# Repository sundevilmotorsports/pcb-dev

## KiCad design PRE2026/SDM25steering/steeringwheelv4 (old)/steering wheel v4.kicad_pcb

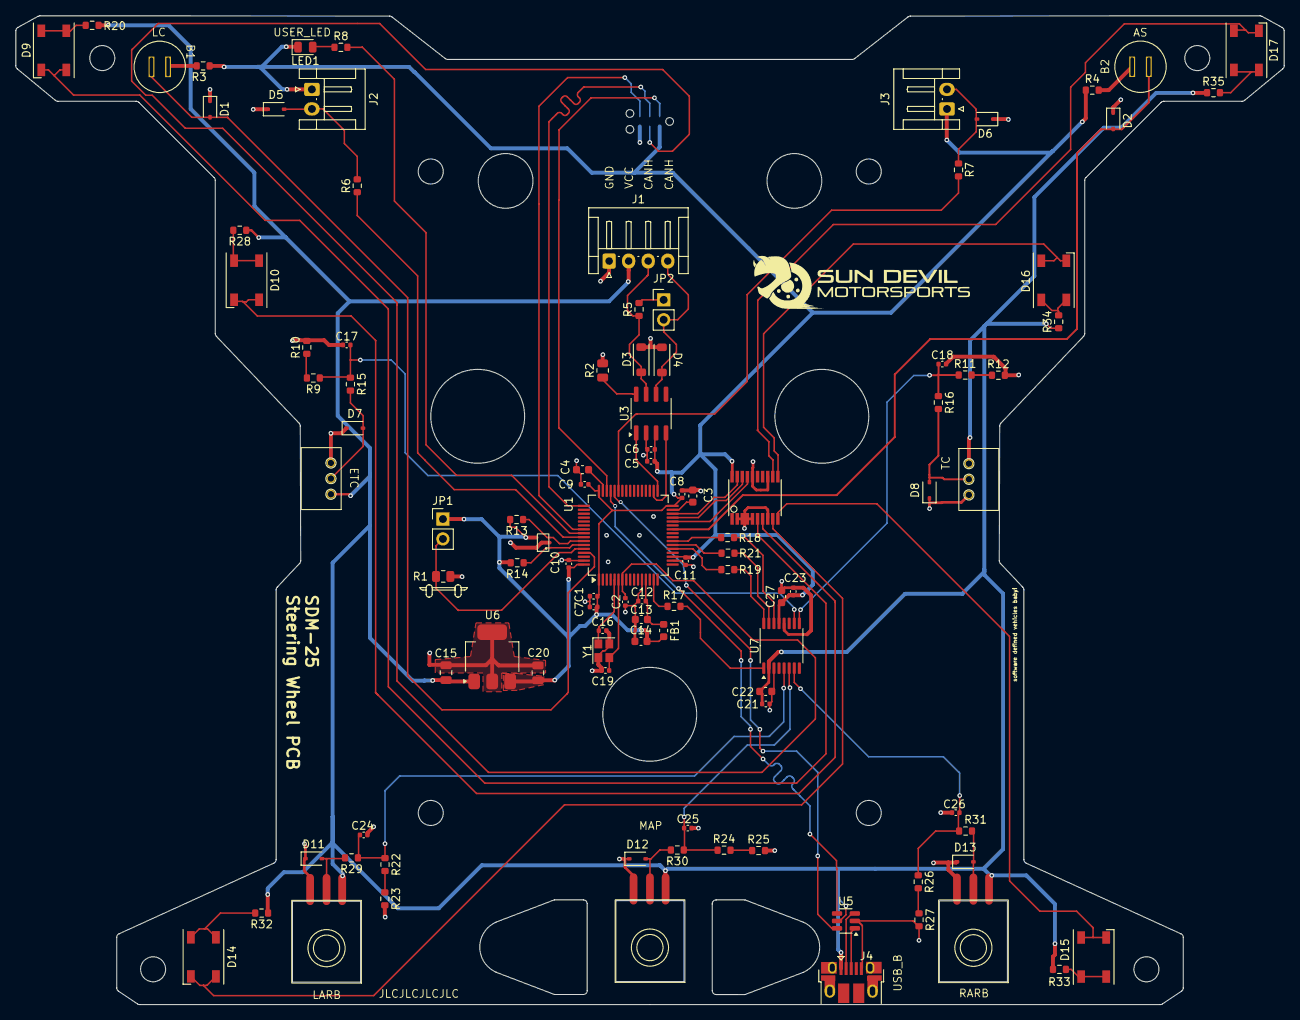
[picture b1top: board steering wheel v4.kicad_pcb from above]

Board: 4 copper layers, 162.2 x 126.4 mm, 111 parts (1 on the bottom side), 73 nets.

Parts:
B1, B2: Conn_01x02; 8631CQD2
C1, C2, C5, C6, C7, C8, C9, C10, C11, C12, C21, C23: 100nF; C_0402_1005Metric
C3, C4: 2.2uF; C_0603_1608Metric
C13, C14, C22, C27: 1uF; C_0603_1608Metric
C15, C20: 10uF; C_0805_2012Metric
C16, C19: 10pF; C_0402_1005Metric
C17, C18, C24, C25, C26: 100n; C_0402_1005Metric
D1, D2, D5, D6, D7, D8, D11, D12, D13: TVS; D_SOD-323
D3, D4: TVS; SOD-123FL
D9, D10, D14, D15, D16, D17: LTST-C235KGKRKT; LED_Cree-PLCC4_5x5mm_CW
FB1: 120R; L_0603_1608Metric
H1, H2, H3, H4, H5, H6, H7, H8: M3; MountingHole_3.2mm_M3
J1: Conn_01x04_Socket; JST_EH_S4B-EH_1x04_P2.50mm_Horizontal
J2, J3: Conn_01x02; JST_EH_S2B-EH_1x02_P2.50mm_Horizontal
J4: USB_B_Micro; USB_Micro-B_Amphenol_10103594-0001LF_Horizontal
J5: Conn_ARM_SWD_TagConnect_TC2030; Tag-Connect_TC2030-IDC-NL_2x03_P1.27mm_Vertical
JP1: BOOT; PinHeader_1x02_P2.54mm_Vertical
JP2: Bus Termination; PinHeader_1x02_P2.54mm_Vertical
LED1: GREEN; LED_0805_2012Metric
POT1, POT2, POT3, POT4, POT5: P081N-271F2CBR10K
R1, R2: 10k; R_0805_2012Metric
R3, R4, R6, R7, R8, R17, R18, R19, R21: 220; R_0603_1608Metric
R5: 120; R_0603_1608Metric
R9, R10, R11, R12, R15, R16, R22, R23, R24, R25, R26, R27, R29, R30, R31: 1k; R_0603_1608Metric
R13, R14: 2.7k; R_0603_1608Metric
R20, R28, R32, R33, R34, R35: 330; R_0603_1608Metric
TLC59108F1: U4; TLC59108F
U1: STM32F405RGT6; LQFP-64_10x10mm_P0.5mm
U3: SN65HVD230; SOIC-8_3.9x4.9mm_P1.27mm
U4: 24LC01BT-E/LT; SC-70-5
U5: USBLC6-2SC6; SOT-23-6
U6: MIC37100-3.3WS; SOT-223-3_TabPin2
U7: ADC128S102; TSSOP-16_4.4x5mm_P0.65mm
Y1: 12MHz; Crystal_SMD_2520-4Pin_2.5x2.0mm

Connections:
+3.3V: C1.2, C5.2, C6.2, C7.2, C8.2, C9.2, C10.2, C11.2, C14.2, C20.1, C23.1, C27.1, FB1.2, J2.1, J3.1, J5.1 (VCC), JP1.1 (A), LED1.1 (K), R3.1, R4.1, R13.2, R14.2, TLC59108F1.20 (VCC), U1.1 (VBAT), U1.19 (VDD), U1.32 (VDD), U1.48 (VDD), U1.64 (VDD), U3.3 (VCC), U4.4 (Vcc), U6.3 (OUT), U7.13 (VDD)
/AIN1: C24.1, R22.1, R29.1, U7.5 (IN1)
/AIN2: C25.1, R24.1, R30.1, U7.6 (IN2)
/AIN3: C26.1, R26.1, R31.1, U7.7 (IN3)
/AIN5: C18.1, R11.1, R16.1, U7.9 (IN5)
/AIN6: C17.1, R9.1, R15.1, U7.10 (IN6)
/B3: D5.2 (A2), J2.2, R6.2
/B4: D6.2 (A2), J3.2, R7.2
/BOOT0: JP1.2 (B), R1.2, U1.60 (BOOT0)
/BUTTON3: R6.1, U1.57 (PB5)
/BUTTON4: R7.1, U1.43 (PA10)
/BUTTON_AS: B2.2, D2.2 (A2), U1.26 (PB0)
/BUTTON_LC: B1.2, D1.2 (A2), U1.61 (PB8)
/CANH: D3.1 (A1), J1.3, R5.1, U3.7 (CANH)
/CANL: D4.2 (A2), J1.4, JP2.2 (B), U3.6 (CANL)
/CRX: U1.33 (PB12), U3.1 (D)
/CS': R17.1, U1.15 (PA1)
/CS_pin: R17.2, U7.1 (~CS)
/CTX: U1.34 (PB13), U3.4 (R)
/D+: J4.3 (D+), U5.1 (I/O1)
/D-: J4.2 (D-), U5.3 (I/O2)
/DIN: R18.2, U7.14 (DIN)
/DOUT: R21.1, U7.15 (DOUT)
/HSE_IN: C16.1, U1.5 (PH0), Y1.1
/HSE_OUT: C19.1, U1.6 (PH1), Y1.3
/I2C1_SCL: R13.1, U1.58 (PB6), U4.3 (SDA)
/I2C1_SDA: R14.1, U1.59 (PB7), U4.1 (SCL)
/LED1: D9.1 (K2), D9.4 (K1), TLC59108F1.6 (OUT0')
/LED2: D10.1 (K2), D10.4 (K1), TLC59108F1.7 (OUT1')
/LED3: D14.1 (K2), D14.4 (K1), TLC59108F1.9 (OUT2')
/LED4: D15.1 (K2), D15.4 (K1), TLC59108F1.10 (OUT3')
/LED5: D16.1 (K2), D16.4 (K1), TLC59108F1.11 (OUT4')
/LED6: D17.1 (K2), D17.4 (K1), TLC59108F1.12 (OUT5')
/MISO: R21.2, U1.22 (PA6)
/MOSI: R18.1, U1.23 (PA7)
/NRST: C2.2, J5.3 (~RESET), U1.7 (NRST)
/POT_ETC: D7.2 (A2), POT1.2 (VDD), R15.2
/POT_LARB: D11.2 (A2), POT3.2 (SIG), R29.2
/POT_MAP: D12.2 (A2), POT4.2 (SIG), R30.2
/POT_RARB: D13.2 (A2), POT5.2 (SIG), R31.2
/POT_TC: D8.2 (A2), POT2.2 (SIG), R16.2
/RESET'_LED: TLC59108F1.17 (RESET'), U1.28 (PB2)
/Rs: R2.1, U3.8 (Rs)
/SCK: R19.1, U1.21 (PA5)
/SCLK: R19.2, U7.16 (SCLK)
/SCL_LED: TLC59108F1.18 (SCL), U1.29 (PB10)
/SDA_LED: TLC59108F1.19 (SDA), U1.30 (PB11)
/SWCLK: J5.4 (SWCLK), U1.49 (PA14)
/SWDIO: J5.2 (SWDIO), U1.46 (PA13)
/SWO: J5.6 (SWO), U1.55 (PB3)
/USB_D+: U1.45 (PA12), U5.4 (I/O2)
/USB_D-: U1.44 (PA11), U5.6 (I/O1)
/USER_LED: R8.2, U1.56 (PB4)
/VCAP_1: C3.1, U1.31 (VCAP_1)
/VCAP_2: C4.2, U1.47 (VCAP_2)
GND: C1.1, C2.1, C3.2, C4.1, C5.1, C6.1, C7.1, C8.1, C9.1, C10.1, C11.1, C12.1, C13.1, C14.1, C15.2, C16.2, C17.2, C18.2, C19.2, C20.2, C21.2, C22.2, C23.2, C24.2, C25.2, C26.2, C27.2, D1.1 (A1), D2.1 (A1), D3.2 (A2), D4.1 (A1), D5.1 (A1), D6.1 (A1), D7.1 (A1), D8.1 (A1), D11.1 (A1), D12.1 (A1), D13.1 (A1), J1.1, J4.5 (GND), J5.5 (GND), POT1.3 (VDD), POT2.3 (GND), POT3.3 (GND), POT4.3 (GND), POT5.3 (GND), R1.1, R2.2, R10.2, R12.2, R23.2, R25.2, R27.2, TLC59108F1.2 (A0), TLC59108F1.3 (A1), TLC59108F1.4 (A2), TLC59108F1.5 (A3), TLC59108F1.8 (GND), TLC59108F1.13 (GND), TLC59108F1.16 (GND), U1.12 (VSSA), U1.18 (VSS), U1.63 (VSS), U3.2 (GND), U4.2 (Vss), U4.5 (WP), U5.2 (GND), U6.2 (GND), U7.3 (AGND), U7.12 (DGND), Y1.2, Y1.4
unnamed: B1.1, R3.2
unnamed: B2.1, R4.2
unnamed: D9.2 (A2), D9.3 (A1), R20.2
unnamed: D10.2 (A2), D10.3 (A1), R28.2
unnamed: D14.2 (A2), D14.3 (A1), R32.2
unnamed: D15.2 (A2), D15.3 (A1), R33.2
unnamed: D16.2 (A2), D16.3 (A1), R34.2
unnamed: D17.2 (A2), D17.3 (A1), R35.2
unnamed: JP2.1 (A), R5.2
unnamed: LED1.2 (A), R8.1
unnamed: R9.2, R10.1
unnamed: R11.2, R12.1
unnamed: R22.2, R23.1
unnamed: R24.2, R25.1
unnamed: R26.2, R27.1
unnamed: C12.2, C13.2, FB1.1, U1.13 (VDDA)
VCC: C15.1, C21.1, C22.1, J1.2, J4.1 (VBUS), POT1.1 (VDD), POT2.1 (VDD), POT3.1 (VDD), POT4.1 (VDD), POT5.1 (VDD), R20.1, R28.1, R32.1, R33.1, R34.1, R35.1, U5.5 (VBUS), U6.1 (IN), U7.2 (VA)

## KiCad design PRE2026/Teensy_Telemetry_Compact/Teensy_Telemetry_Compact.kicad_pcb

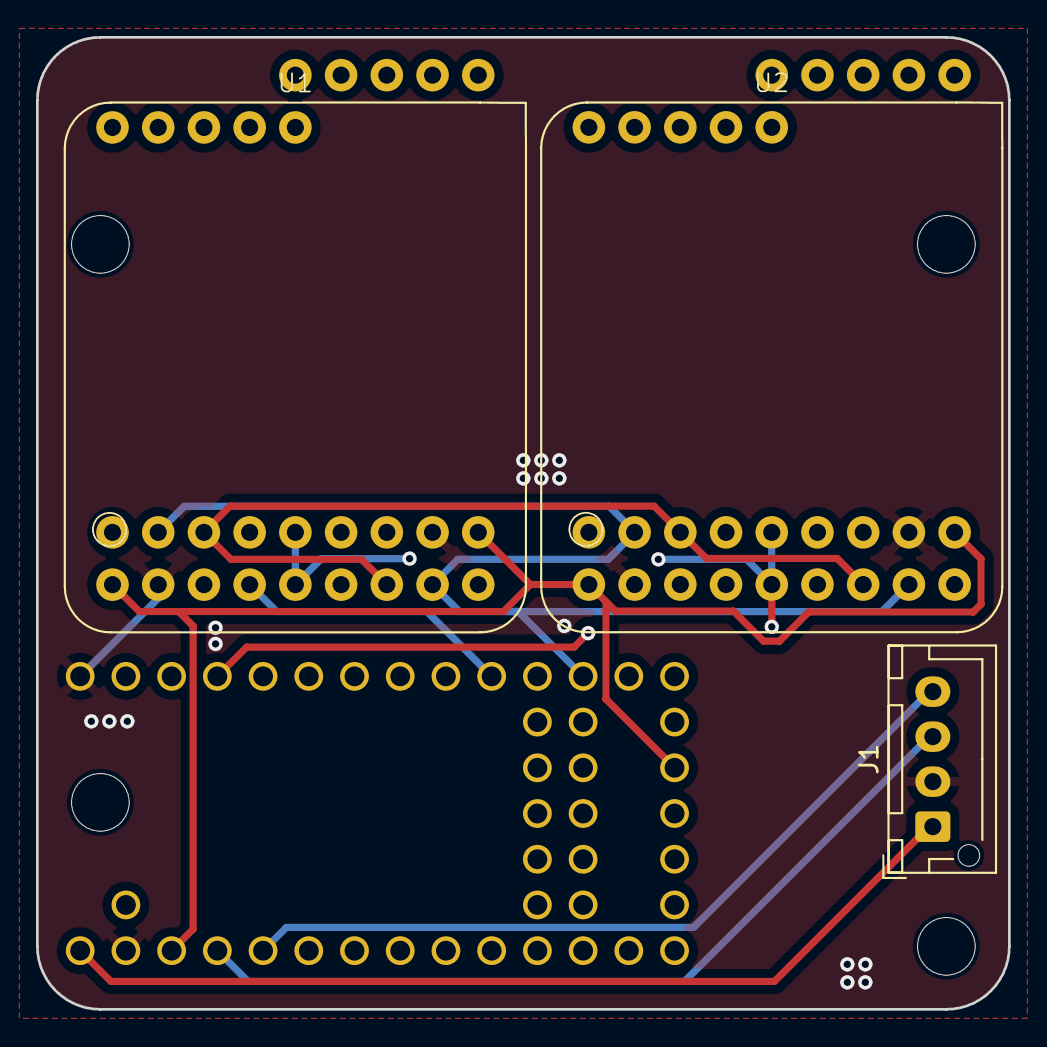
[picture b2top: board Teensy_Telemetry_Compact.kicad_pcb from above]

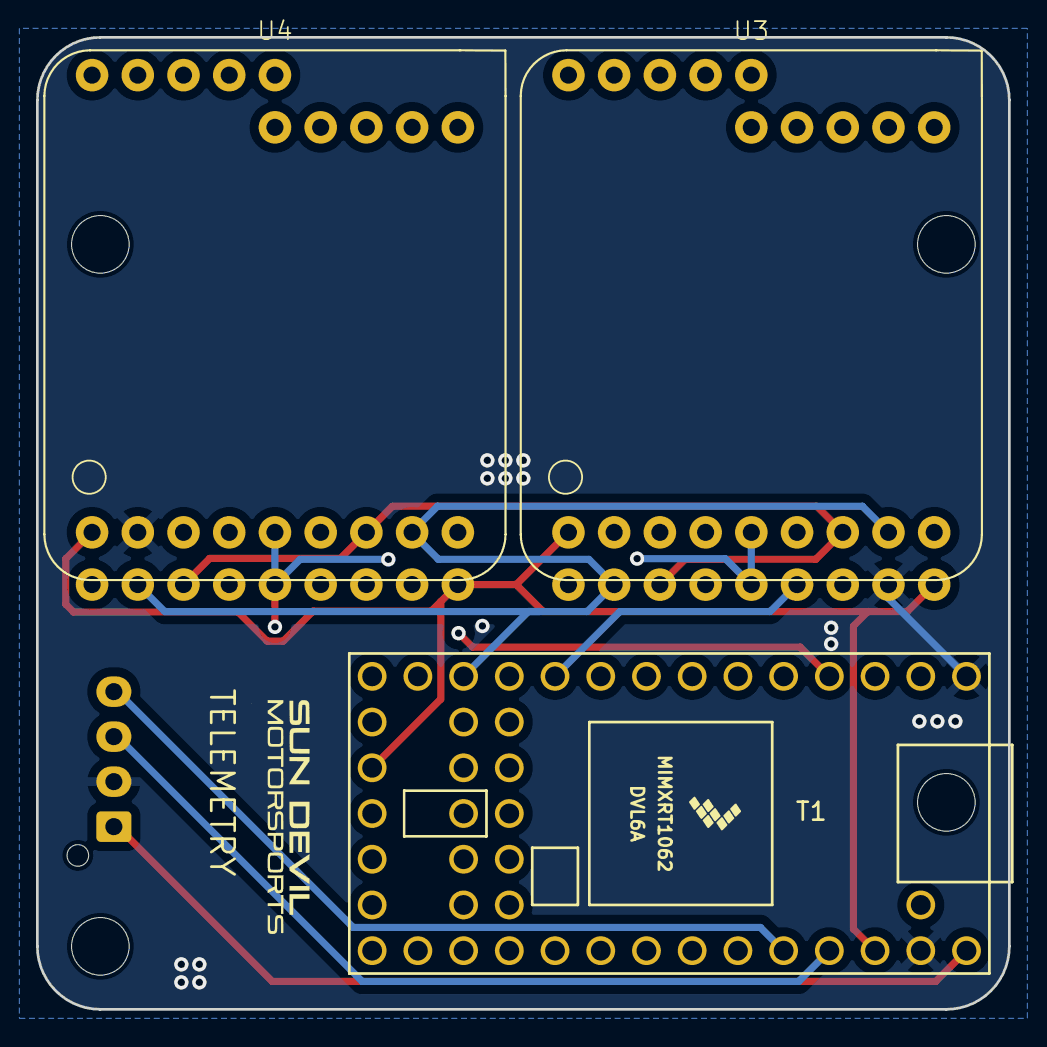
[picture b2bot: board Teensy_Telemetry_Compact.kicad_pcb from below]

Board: 4 copper layers, 54.0 x 54.0 mm, 10 parts (3 on the bottom side), 15 nets.

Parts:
H4, H4#2, H4#3, H4#4: M3; MountingHole_3.2mm_M3
J1: CAN_DaisyChain; JST_XH_B4B-XH-AM_1x04_P2.50mm_Vertical
T1: Teensy4.0; Teensy40
U1, U2, U3, U4: RFM95W

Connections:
+3.3V: T1.16 (3V3), T1.31 (3V3), U1.1 (Vin), U2.1 (Vin), U3.1 (Vin), U4.1 (Vin)
+5V: J1.1, T1.33 (VIN)
/CANH: J1.3, T1.30 (23_A9_CRX1_MCLK1)
/CANL: J1.4, T1.29 (22_A8_CTX1)
/CS: T1.12 (10_CS_MQSR), U1.8 (CS), U2.8 (CS), U3.8 (CS), U4.8 (CS)
/EN: T1.22 (15_A1_RX3_SPDIF_IN), U1.3 (EN), U2.3 (EN), U3.3 (EN), U4.3 (EN)
/IRQ1: T1.10 (8_TX2_IN1), U1.4 (G0)
/IRQ2: T1.4 (2_OUT2), U2.4 (G0)
/IRQ3: T1.28 (21_A7_RX5_BCLK1), U3.4 (G0)
/IRQ4: T1.21 (14_A0_TX3_SPDIF_OUT), U4.4 (G0)
/MISO: T1.14 (12_MISO_MQSL), U1.6 (MISO), U2.6 (MISO), U3.6 (MISO), U4.6 (MISO)
/MOSI: T1.13 (11_MOSI_CTX1), U1.7 (MOSI), U2.7 (MOSI), U3.7 (MOSI), U4.7 (MOSI)
/Reset: T1.11 (9_OUT1C), U1.9 (RST), U2.9 (RST), U3.9 (RST), U4.9 (RST)
/SCK: T1.20 (13_SCK_CRX1_LED), U1.5 (SCK), U2.5 (SCK), U3.5 (SCK), U4.5 (SCK)
GND: J1.2, T1.1 (GND), T1.32 (GND), U1.2 (GND), U2.2 (GND), U3.2 (GND), U4.2 (GND)

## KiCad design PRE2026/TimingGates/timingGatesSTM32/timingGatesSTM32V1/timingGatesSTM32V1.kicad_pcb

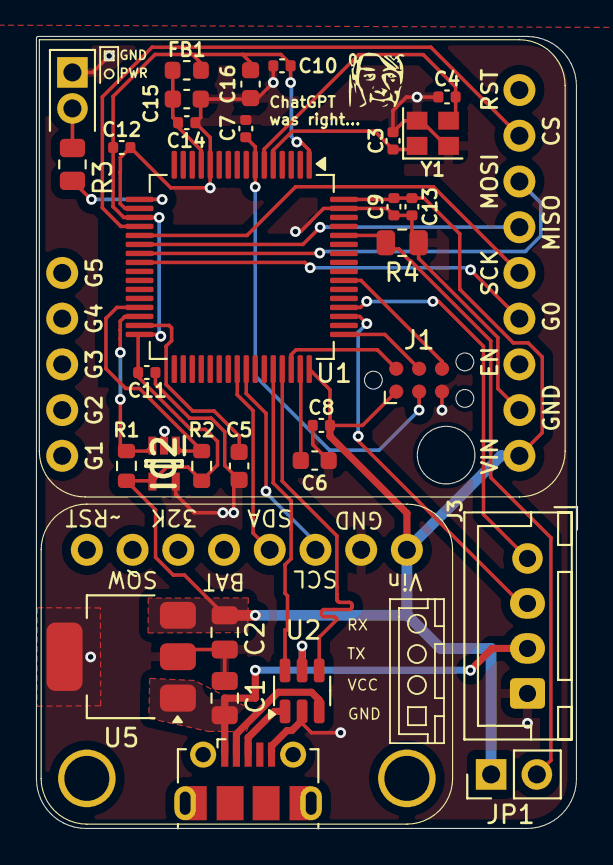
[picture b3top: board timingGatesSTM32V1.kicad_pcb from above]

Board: 4 copper layers, 30.0 x 44.0 mm, 34 parts (0 on the bottom side), 30 nets.

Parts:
C1, C2: 10uF; C_0805_2012Metric
C3, C4: 10pF; C_0402_1005Metric
C5, C6: 2.2uF; C_0603_1608Metric
C7, C8, C9, C10, C11, C12, C13, C14: 100nF; C_0402_1005Metric
C15, C16: 1uF; C_0603_1608Metric
D1: RED (floating); LED_0805_2012Metric
FB1: 120R; L_0603_1608Metric
H1: M3; MountingHole_3.2mm_M3
IC2: 24LC01BT-E_LT; SOT65P210X110-5N
J1: Conn_ARM_SWD_TagConnect_TC2030; Tag-Connect_TC2030-IDC-NL_2x03_P1.27mm_Vertical
J2: USB_B_Micro; USB_Micro-B_Molex-105017-0001
J3: Conn_01x04_Socket; JST_XH_B4B-XH-A_1x04_P2.50mm_Vertical
JP1: BOOT; PinHeader_1x02_P2.54mm_Vertical
R1, R2: 2.7k; R_0603_1608Metric
R3: 220; R_0805_2012Metric
R4: 10k; R_0805_2012Metric
U1: STM32F405RGT6; LQFP-64_10x10mm_P0.5mm
U2: USBLC6-2SC6; SOT-23-6
U3: RFM95W
U4: DS3231
U5: MIC37100-3.3WS; SOT-223-3_TabPin2
Y1: 12MHz; Crystal_SMD_2520-4Pin_2.5x2.0mm

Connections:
+3.3V: C2.1, C8.2, C9.2, C10.2, C11.2, C12.2, C13.2, C16.2, FB1.2, IC2.4 (VCC), J1.1 (VCC), JP1.1 (A), R1.2, R2.2, U1.1 (VBAT), U1.19 (VDD), U1.32 (VDD), U1.48 (VDD), U1.64 (VDD), U3.1 (Vin), U4.1 (Vin), U5.3 (OUT)
/BOOT0: JP1.2 (B), R4.2, U1.60 (BOOT0)
/G0: U1.24 (PC4), U3.4 (G0)
/HSE_IN: C3.1, U1.5 (PH0), Y1.1
/HSE_OUT: C4.1, U1.6 (PH1), Y1.3
/I2C2_SCL: IC2.1 (SCL), R2.1, U1.29 (PB10)
/I2C2_SDA: IC2.3 (SDA), R1.1, U1.30 (PB11)
/I2C3_SCL: U1.41 (PA8), U4.3 (SCL)
/I2C3_SDA: U1.40 (PC9), U4.4 (SDA)
/NRST: C7.2, J1.3 (~RESET), U1.7 (NRST)
/SPI1_MISO: U1.22 (PA6), U3.6 (MISO)
/SPI1_MOSI: U1.23 (PA7), U3.7 (MOSI)
/SPI1_NSS: U1.20 (PA4), U3.8 (CS)
/SPI1_SCK: U1.21 (PA5), U3.5 (SCK)
/SWCLK: J1.4 (SWCLK), U1.49 (PA14)
/SWDIO: J1.2 (SWDIO), U1.46 (PA13)
/SWO: J1.6 (SWO), U1.55 (PB3)
/USART3_RX: J3.1, U1.52 (PC11)
/USART3_TX: J3.2, U1.51 (PC10)
/USB_D+: U1.45 (PA12), U2.4 (I/O2)
/USB_D-: U1.44 (PA11), U2.6 (I/O1)
/VCAP_1: C5.1, U1.31 (VCAP_1)
/VCAP_2: C6.2, U1.47 (VCAP_2)
GND: C1.2, C2.2, C3.2, C4.2, C5.2, C6.1, C7.1, C8.1, C9.1, C10.1, C11.1, C12.1, C13.1, C14.1, C15.1, C16.1, D1.1 (K), IC2.2 (Vss), IC2.5 (WP), J1.5 (GND), J2.5 (GND), J3.4, R4.1, U1.12 (VSSA), U1.18 (VSS), U1.63 (VSS), U2.2 (GND), U3.2 (GND), U4.2 (GND), U5.2 (GND), Y1.2, Y1.4
unnamed: D1.2 (A), R3.1
unnamed: J2.3 (D+), U2.1 (I/O1)
unnamed: J2.2 (D-), U2.3 (I/O2)
unnamed: R3.2, U1.17 (PA3)
unnamed: C14.2, C15.2, FB1.1, U1.13 (VDDA)
VCC: C1.1, J2.1 (VBUS), J3.3, U2.5 (VBUS), U5.1 (IN)

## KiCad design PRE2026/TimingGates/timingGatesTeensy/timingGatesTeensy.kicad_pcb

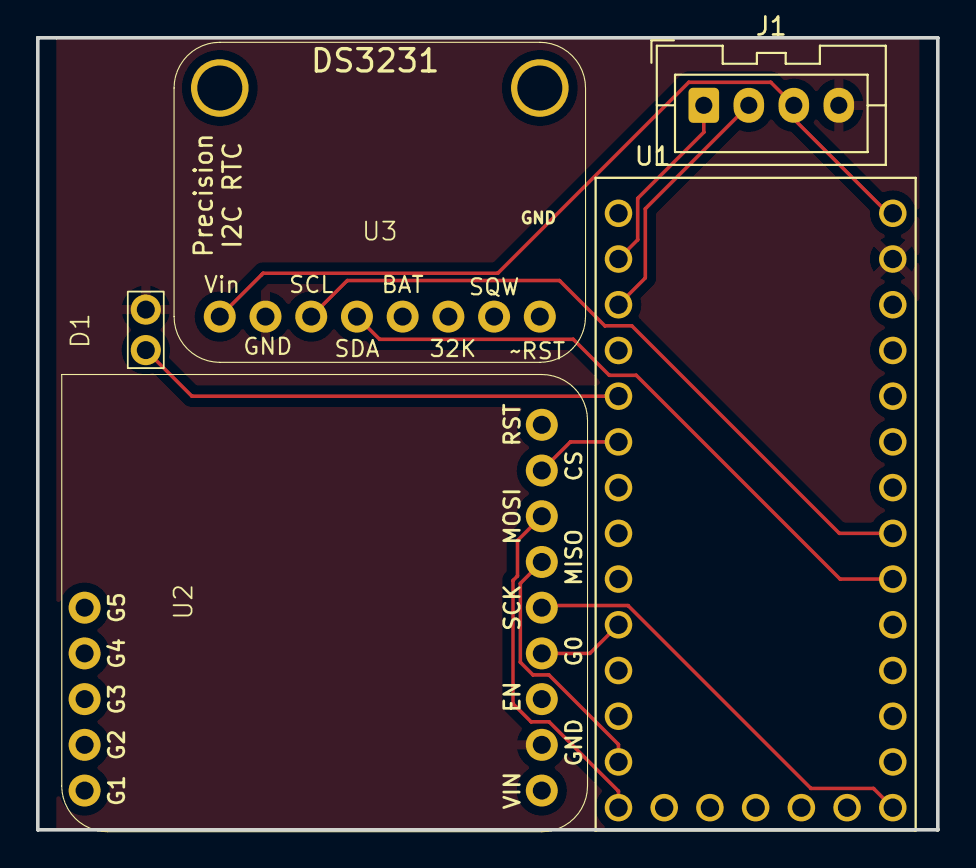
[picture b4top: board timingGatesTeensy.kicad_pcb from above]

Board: 4 copper layers, 50.0 x 44.0 mm, 5 parts (0 on the bottom side), 10 nets.

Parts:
D1: LED (floating)
J1: JST_XA_B04B-XASK-1_1x04_P2.50mm_Vertical
U1: DEV-15583; Teensy4.0
U2: RFM95W
U3: DS3231

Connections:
/CS: U1.4, U2.8
/G0: U1.8, U2.4
/MISO: U1.11, U2.6
/MOSI: U1.12, U2.7
/SCK: U1.13, U2.5
/SCL: U1.19, U3.3
/SDA: U1.18, U3.4
GND: D1.2, J1.4, U1.G3, U2.2, U3.2
unnamed: D1.1, U1.3
VCC: J1.3, U1.VIN, U2.1, U3.1

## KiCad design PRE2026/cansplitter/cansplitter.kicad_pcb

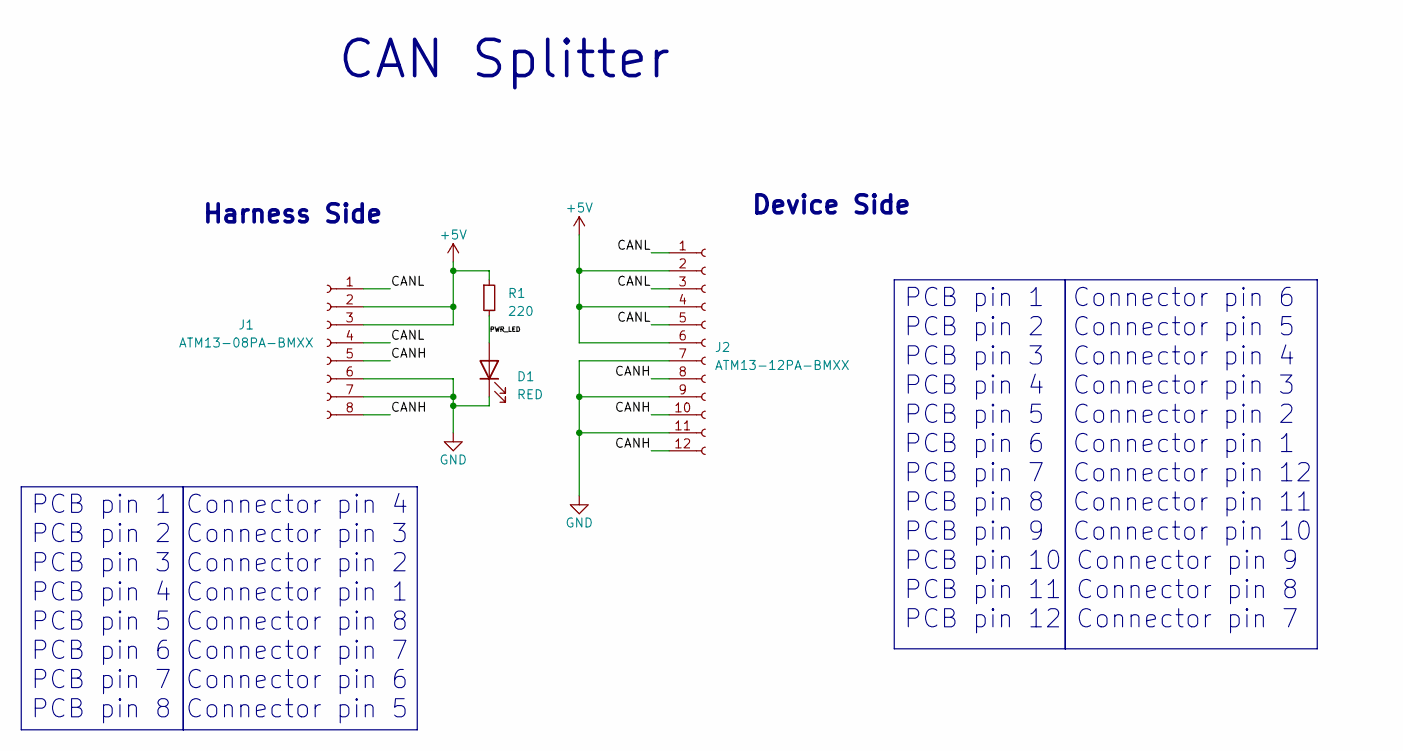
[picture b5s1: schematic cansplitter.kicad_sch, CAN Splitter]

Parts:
D1: RED; LED_1206_3216Metric
J1: ATM13-08PA-BMXX
J2: ATM13-12PA-BMXX
R1: 220; R_1206_3216Metric

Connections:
+5V: J1.2, J1.3, J2.2, J2.4, J2.6, R1.1
/CANH: J1.5, J1.8, J2.8, J2.10, J2.12
/CANL: J1.1, J1.4, J2.1, J2.3, J2.5
/PWR_LED: D1.2 (A), R1.2
GND: D1.1 (K), J1.6, J1.7, J2.7, J2.9, J2.11

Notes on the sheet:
PCB pin 1 Connector pin 6 PCB pin 2 Connector pin 5 PCB pin 3 Connector pin 4 PCB pin 4 Connector pin 3 PCB pin 5 Connector pin 2 PCB pin 6 Connector pin 1 PCB pin 7 Connector pin 12 PCB pin 8 Connector pin 11 PCB pin 9 Connector pin 10 PCB pin 10 Connector pin 9 PCB pin 11 Connector pin 8 PCB pin 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
Harness Side
Device Side
CAN Splitter
PCB pin 1 Connector pin 4 PCB pin 2 Connector pin 3 PCB pin 3 Connector pin 2 PCB pin 4 Connector pin 1 PCB pin 5 Connector pin 8 PCB pin 6 Connector pin 7 PCB pin 7 Connector pin 6 PCB pin 8 Connector pin 5

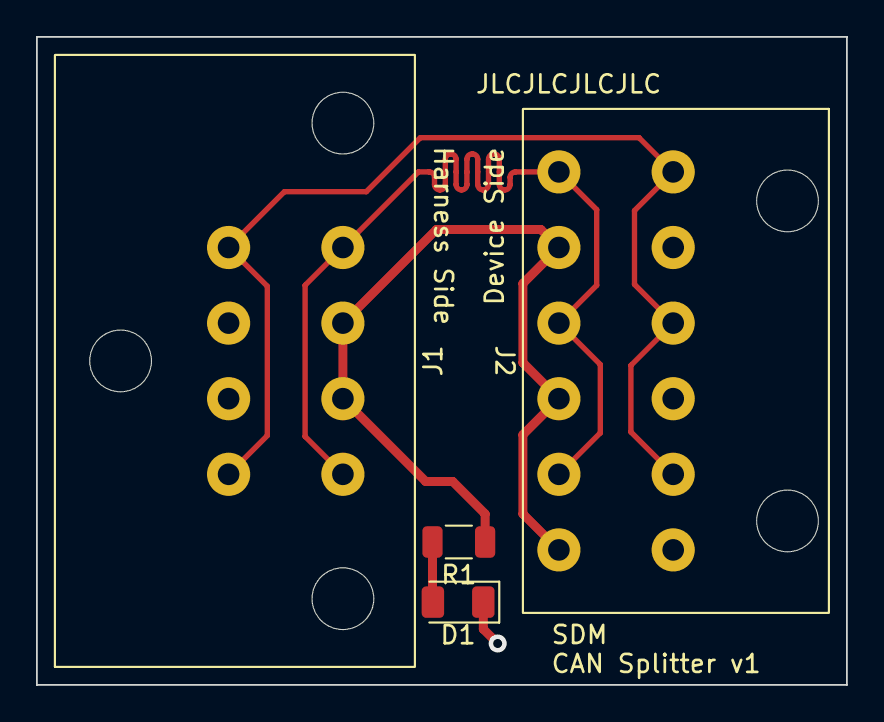
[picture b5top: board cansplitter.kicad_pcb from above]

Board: 2 copper layers, 45.0 x 36.0 mm, 4 parts (0 on the bottom side), 5 nets.

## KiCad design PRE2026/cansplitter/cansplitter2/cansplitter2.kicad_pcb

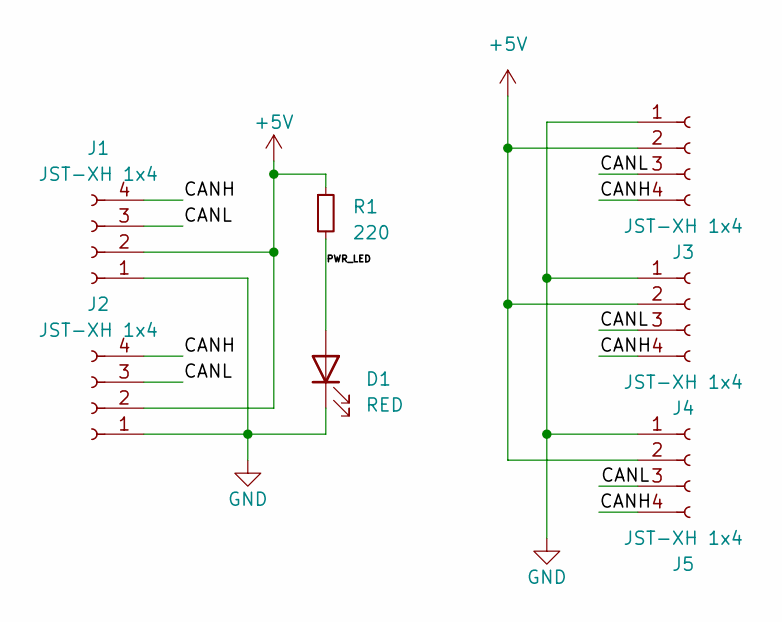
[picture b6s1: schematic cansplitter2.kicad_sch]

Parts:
D1: RED; LED_1206_3216Metric
J1, J2, J3, J4, J5: JST-XH 1x4; JST_XH_B4B-XH-A_1x04_P2.50mm_Vertical
R1: 220; R_1206_3216Metric

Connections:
+5V: J1.2, J2.2, J3.2, J4.2, J5.2, R1.1
/CANH: J1.4, J2.4, J3.4, J4.4, J5.4
/CANL: J1.3, J2.3, J3.3, J4.3, J5.3
/PWR_LED: D1.2 (A), R1.2
GND: D1.1 (K), J1.1, J2.1, J3.1, J4.1, J5.1

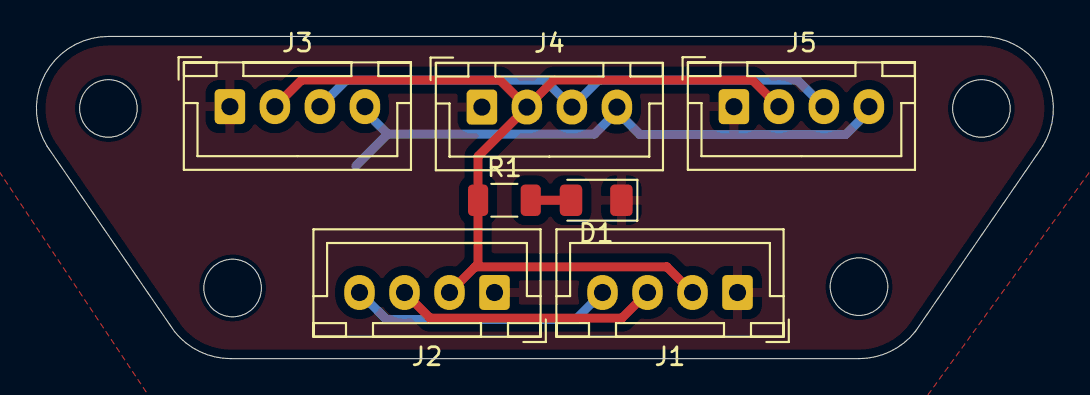
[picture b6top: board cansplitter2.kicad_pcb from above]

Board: 2 copper layers, 56.5 x 17.9 mm, 11 parts (0 on the bottom side), 5 nets.

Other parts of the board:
H2, H2#2, H2#3, H2#4: M3; MountingHole_3.2mm_M3

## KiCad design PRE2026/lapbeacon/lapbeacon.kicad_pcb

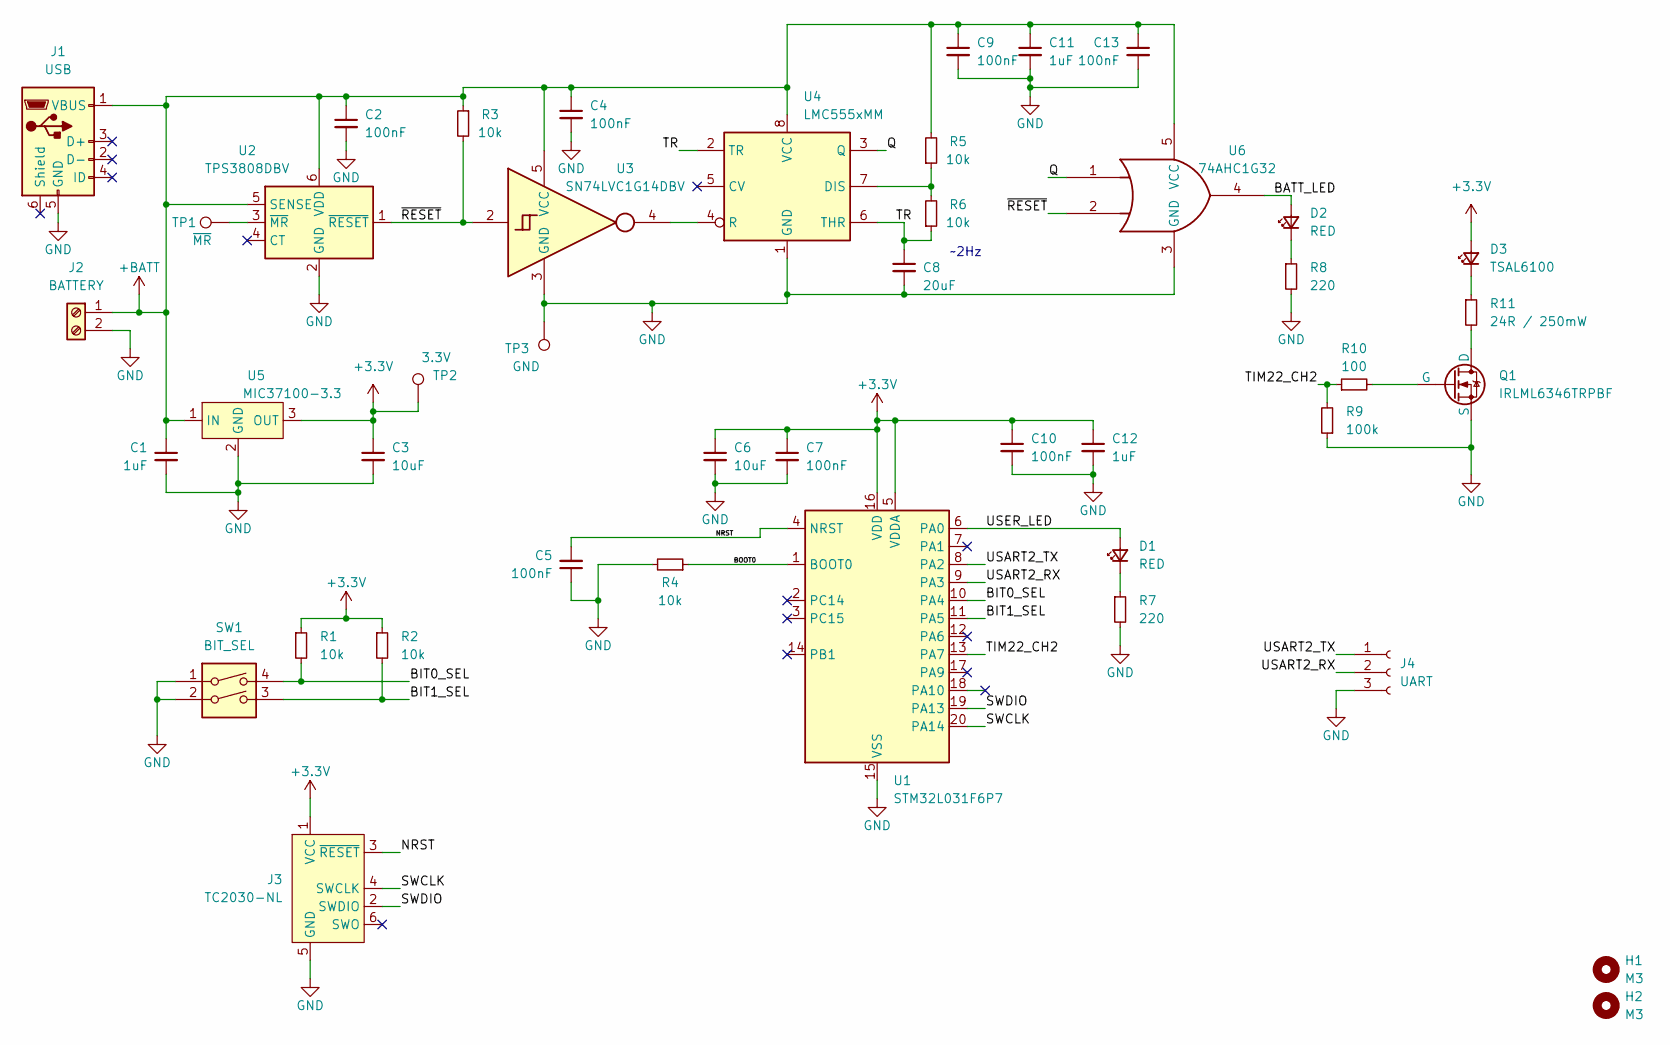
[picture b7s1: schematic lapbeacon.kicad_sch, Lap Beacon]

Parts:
C1, C11, C12: 1uF; C_0603_1608Metric
C2, C4, C5, C7, C9, C10, C13: 100nF; C_0402_1005Metric
C3, C6: 10uF; C_0805_2012Metric
C8: 20uF; C_0603_1608Metric
D1, D2: RED; LED_0603_1608Metric
D3: TSAL6100; LED_D5.0mm_IRBlack
H1, H2: M3; MountingHole_3.2mm_M3
J1: USB; USB_Micro-B_Molex-105017-0001
J2: BATTERY; TerminalBlock_TE_282834-2_1x02_P2.54mm_Horizontal
J3: TC2030-NL; Tag-Connect_TC2030-IDC-NL_2x03_P1.27mm_Vertical
J4: UART; JST_XH_B3B-XH-A_1x03_P2.50mm_Vertical
Q1: IRLML6346TRPBF; SOT-23
R1, R2: 10k; R_0805_2012Metric
R3, R5, R6: 10k; R_0402_1005Metric
R4: 10k; R_0603_1608Metric
R7, R8: 220; R_0603_1608Metric
R9: 100k; R_0805_2012Metric
R10: 100; R_0603_1608Metric
R11: 24R / 250mW; R_0603_1608Metric
SW1: BIT_SEL; 2454985-3
TP1: ~{MR}; TestPoint_Pad_1.0x1.0mm
TP2: 3.3V; TestPoint_Pad_1.0x1.0mm
TP3: GND; TestPoint_Pad_1.0x1.0mm
U1: STM32L031F6P7; TSSOP-20_4.4x6.5mm_P0.65mm
U2: TPS3808DBV; SOT-23-6
U3: SN74LVC1G14DBV; SOT-23-5
U4: LMC555xMM; VSSOP-8_3.0x3.0mm_P0.65mm
U5: MIC37100-3.3; SOT-223-3_TabPin2
U6: 74AHC1G32; SOT-23-5

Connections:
+3.3V: C3.1, C6.1, C7.1, C10.1, C12.1, D3.2 (A), J3.1 (VCC), R1.1, R2.1, TP2.1, U1.5 (VDDA), U1.16 (VDD), U5.3 (OUT)
+BATT: C1.1, C2.1, C4.1, C9.1, C11.1, C13.1, J1.1 (VBUS), J2.1, R3.1, R5.2, U2.5 (SENSE), U2.6 (VDD), U3.5 (VCC), U4.8 (VCC), U5.1 (IN), U6.5 (VCC)
/BATT_LED: D2.2 (A), U6.4
/BIT0_SEL: R1.2, SW1.4, U1.10 (PA4)
/BIT1_SEL: R2.2, SW1.3, U1.11 (PA5)
/BOOT0: R4.1, U1.1 (BOOT0)
/NRST: C5.2, J3.3 (~RESET), U1.4 (NRST)
/Q: U4.3 (Q), U6.1
/SWCLK: J3.4 (SWCLK), U1.20 (PA14)
/SWDIO: J3.2 (SWDIO), U1.19 (PA13)
/TIM22_CH2: R9.2, R10.1, U1.13 (PA7)
/TR: C8.1, R6.1, U4.2 (TR), U4.6 (THR)
/USART2_RX: J4.2, U1.9 (PA3)
/USART2_TX: J4.1, U1.8 (PA2)
/USER_LED: D1.2 (A), U1.6 (PA0)
/~RESET: R3.2, U2.1 (~RESET), U3.2, U6.2
GND: C1.2, C2.2, C3.2, C4.2, C5.1, C6.2, C7.2, C8.2, C9.2, C10.2, C11.2, C12.2, C13.2, J1.5 (GND), J2.2, J3.5 (GND), J4.3, Q1.3 (S), R4.2, R7.2, R8.2, R9.1, SW1.1, SW1.2, TP3.1, U1.15 (VSS), U2.2 (GND), U3.3 (GND), U4.1 (GND), U5.2 (GND), U6.3 (GND)
unnamed: D1.1 (K), R7.1
unnamed: D2.1 (K), R8.1
unnamed: D3.1 (K), R11.1
unnamed: Q1.1 (D), R11.2
unnamed: Q1.2 (G), R10.2
unnamed: TP1.1, U2.3 (~MR)
unnamed: R5.1, R6.2, U4.7 (DIS)
unnamed: U3.4, U4.4 (R)

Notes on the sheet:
~2Hz

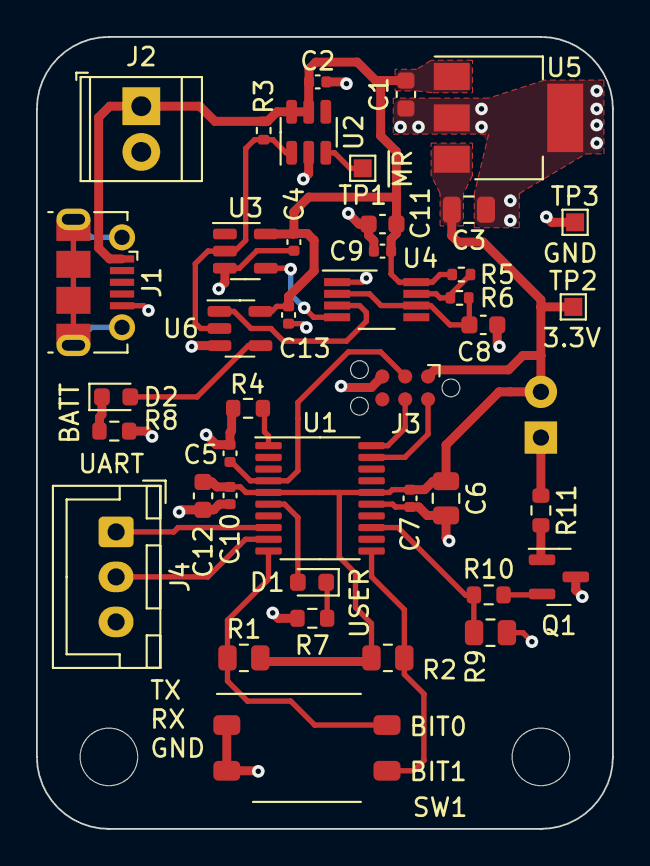
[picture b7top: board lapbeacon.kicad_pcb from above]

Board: 2 copper layers, 32.0 x 44.0 mm, 44 parts (1 on the bottom side), 25 nets.
